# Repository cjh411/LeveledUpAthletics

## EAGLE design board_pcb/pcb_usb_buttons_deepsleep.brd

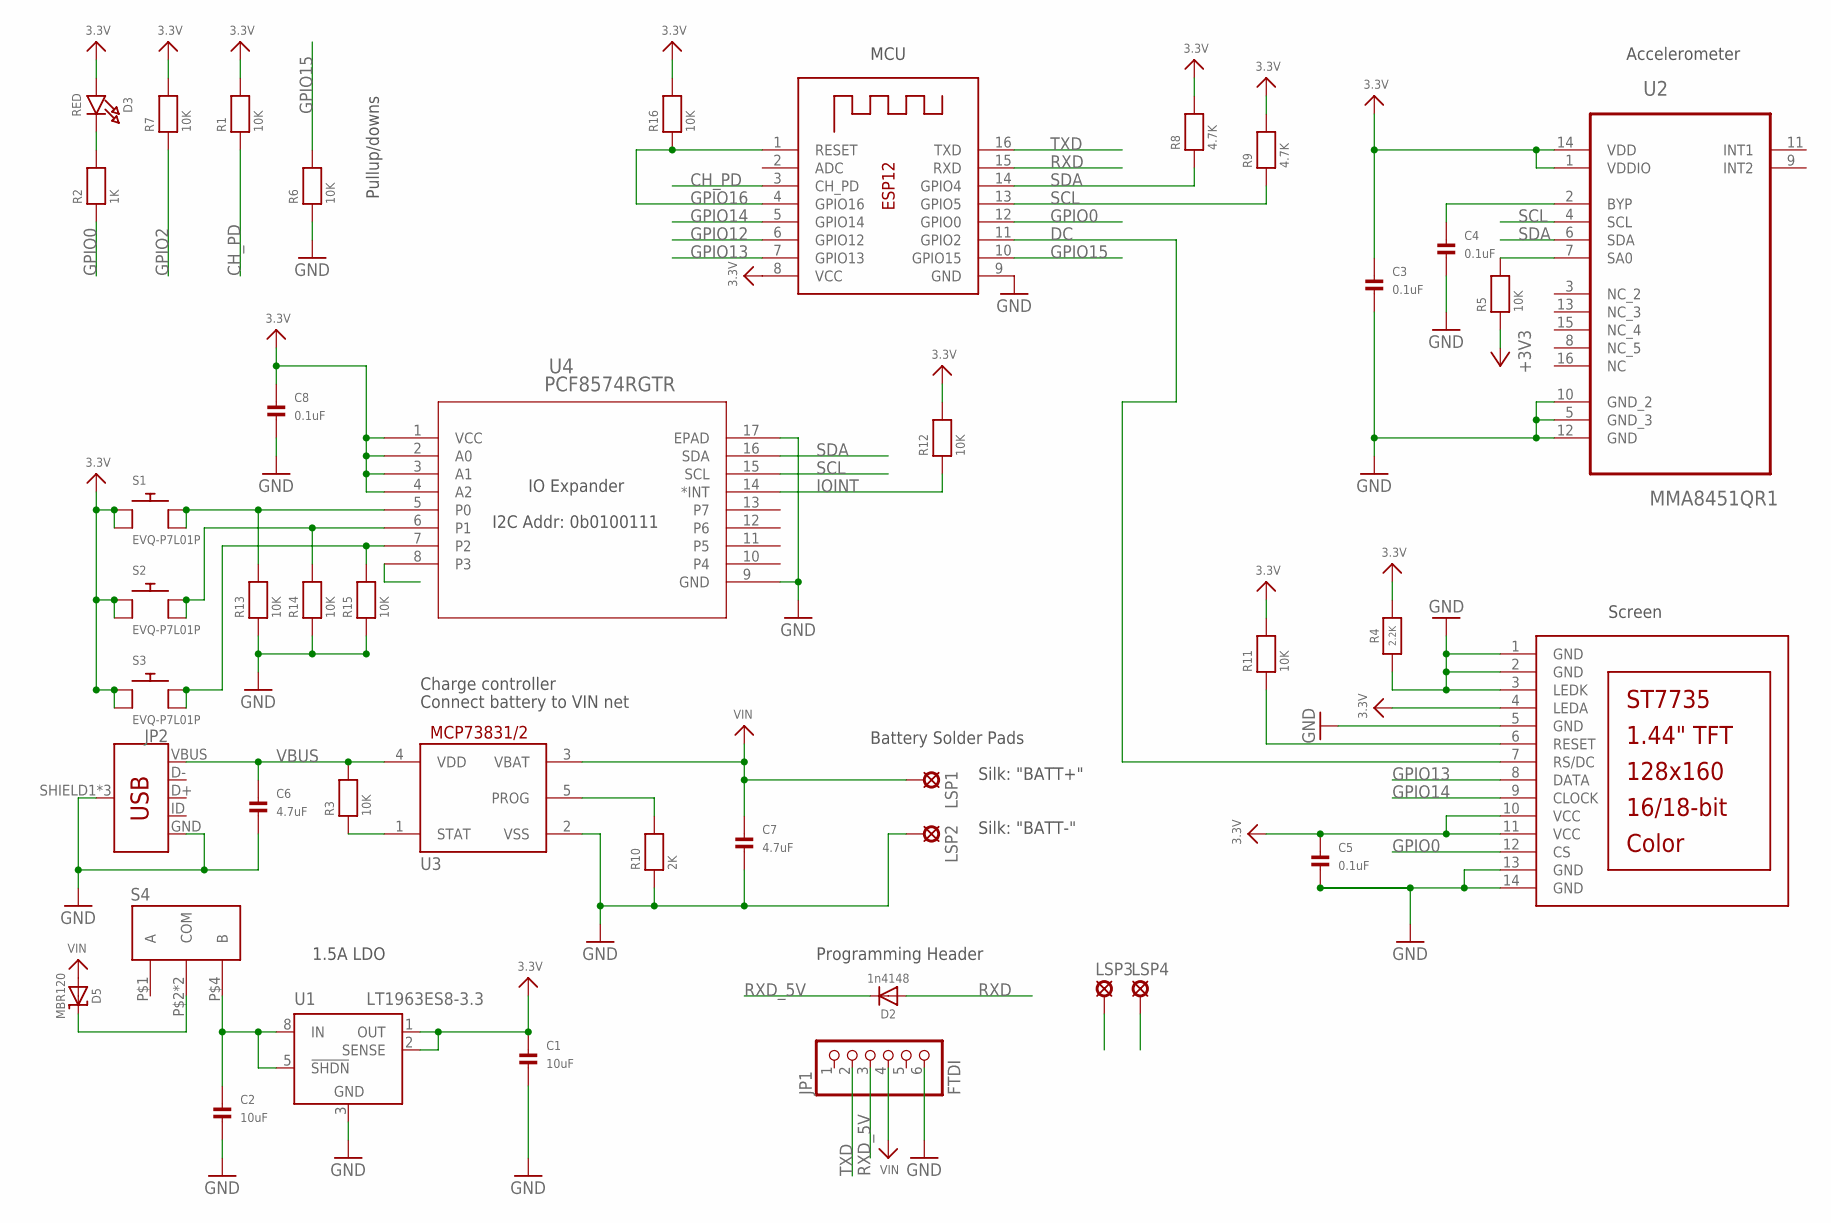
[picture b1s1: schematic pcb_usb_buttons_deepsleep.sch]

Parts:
C1, C2: 10uF; 0805
C3, C4, C5, C8: 0.1uF; 0805
C6, C7: 4.7uF; 0805
D2: 1n4148; SOD-323
D3: RED; CHIPLED_0805_NOOUTLINE
D5: MBR120; SOD-123
JP1: FTDI; 1X06_ROUND_70
JP2: USB_MICRO-B_FEMALE-SMT; USB-B-MICRO-SMD
LSP1, LSP2, LSP3, LSP4: LSP10
R1, R3, R5, R6, R7, R11, R12, R13, R14, R15, R16: 10K; 0805
R2: 1K; 0805
R4: 2.2K; 0805-NO
R8, R9: 4.7K; 0805
R10: 2K; 0805
S1, S2, S3: EVQ-P7L01P; EVQ-P7L
S4: ESD165236
TFT1: DISP_LCD_ST7735_1.44IN; TFT_1.44IN_128_128
U1: LT1963ES8-3.3; SOIC8
U2: MMA8451QR1; QFN50P300X300X100-16N
U3: MCP73831/OT; SOT23-5L
U4: PCF8574RGTR; RGT16_1P6X1P6
X1: ESP-12

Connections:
3.3V: C1.1, C3.1, C5.1, C8.1, D3.A, R1.2, R4.2, R5.1, R7.2, R8.2, R9.2, R11.2, R12.2, R16.2, S1.P$1, S1.P$1@2, S2.P$1, S2.P$1@2, S3.P$1, S3.P$1@2, TFT1.4 (LEDA), TFT1.10 (VCC), TFT1.11 (VCC), U1.1 (OUT), U1.2 (SENSE), U2.1 (VDDIO), U2.14 (VDD), U4.1 (VCC), U4.2 (A0), U4.3 (A1), U4.4 (A2), X1.8 (VCC)
CH_PD: R1.1, X1.3 (CH_PD)
DC: TFT1.7 (RS/DC), X1.11 (GPIO2)
DISC: LSP3.MP, U4.8 (P3)
GND: C1.2, C2.2, C3.2, C4.2, C5.2, C6.2, C7.2, C8.2, JP1.6, JP2.GND, JP2.SHIELD1 (SHIELD), JP2.SHIELD2 (SHIELD), JP2.SHIELD3 (SHIELD), LSP2.MP, LSP4.MP, R4.1, R6.1, R10.1, R13.1, R14.1, R15.1, TFT1.1 (GND), TFT1.2 (GND), TFT1.3 (LEDK), TFT1.5 (GND), TFT1.13 (GND), TFT1.14 (GND), U1.3 (GND), U1.6 (GND), U1.7 (GND), U2.5 (GND_3), U2.10 (GND_2), U2.12 (GND), U3.2 (VSS), U4.9 (GND), U4.17 (EPAD), X1.9 (GND)
GPIO0: R2.1, TFT1.12 (CS), X1.12 (GPIO0)
GPIO2: R7.1
GPIO12: X1.6 (GPIO12)
GPIO13: TFT1.8 (DATA), X1.7 (GPIO13)
GPIO14: TFT1.9 (CLOCK), X1.5 (GPIO14)
GPIO15: R6.2, X1.10 (GPIO15)
GPIO16: R16.1, X1.1 (RESET), X1.4 (GPIO16)
IOINT: R12.1, U4.14 (*INT)
unnamed: D3.C, R2.2
unnamed: C2.1, S4.P$4 (B), U1.5 (!SHDN), U1.8 (IN)
unnamed: R11.1, TFT1.6 (RESET)
unnamed: R3.1, U3.1 (STAT)
unnamed: R10.2, U3.5 (PROG)
unnamed: R13.2, S1.P$2, S1.P$2@2, U4.5 (P0)
unnamed: R5.2, U2.7 (SA0)
unnamed: C4.1, U2.2 (BYP)
unnamed: R14.2, S2.P$2, S2.P$2@2, U4.6 (P1)
unnamed: R15.2, S3.P$2, S3.P$2@2, U4.7 (P2)
unnamed: D5.C, S4.P$2 (COM), S4.P$3 (COM)
RXD: D2.A, X1.15 (RXD)
RXD_5V: D2.C, JP1.3
SCL: R9.1, U2.4 (SCL), U4.15 (SCL), X1.13 (GPIO5)
SDA: R8.1, U2.6 (SDA), U4.16 (SDA), X1.14 (GPIO4)
TXD: JP1.2, X1.16 (TXD)
VBUS: C6.1, JP2.VBUS, R3.2, U3.4 (VDD)
VIN: C7.1, D5.A, JP1.4, LSP1.MP, U3.3 (VBAT)

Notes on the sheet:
Pullup/downs
MCU
Accelerometer
Screen
1.5A LDO
Programming Header
Charge controller
Connect battery to VIN net
IO Expander
I2C Addr: 0b0100111
Battery Solder Pads
Silk: "BATT+"
Silk: "BATT-"

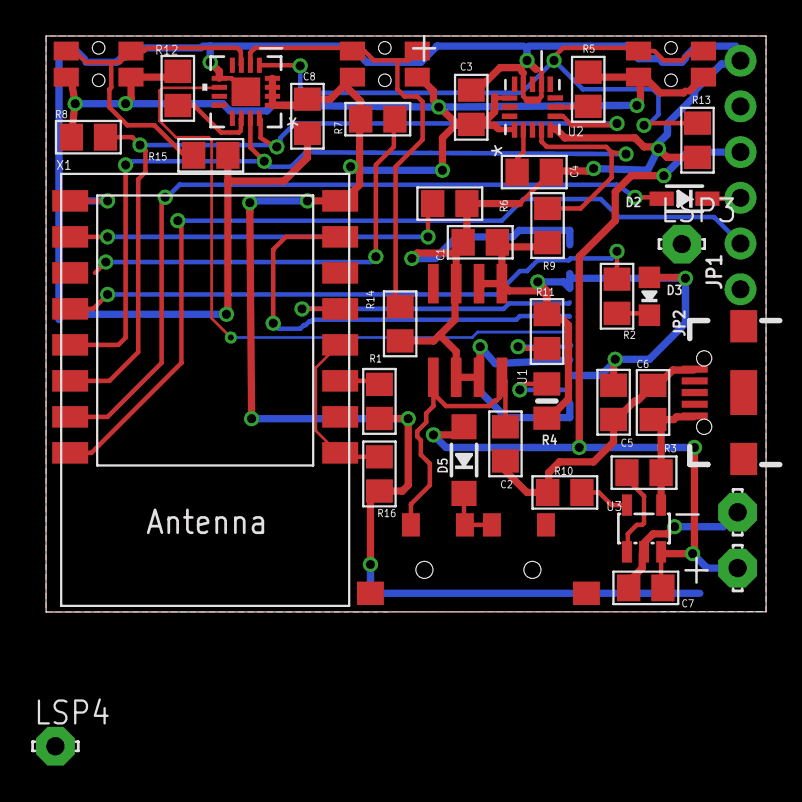
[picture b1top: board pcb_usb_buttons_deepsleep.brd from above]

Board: 2 copper layers, 40.0 x 32.0 mm, 43 parts (1 on the bottom side), 29 nets.

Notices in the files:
parts and their libraries:
microbuilder: This work is placed in the public domain, and may be freely used for commercial and non-commercial work with the following conditions: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
SparkFun-Connectors: Licensing: Creative Commons ShareAlike 4.0 International - https://creativecommons.org/licenses/by-sa/4.0
